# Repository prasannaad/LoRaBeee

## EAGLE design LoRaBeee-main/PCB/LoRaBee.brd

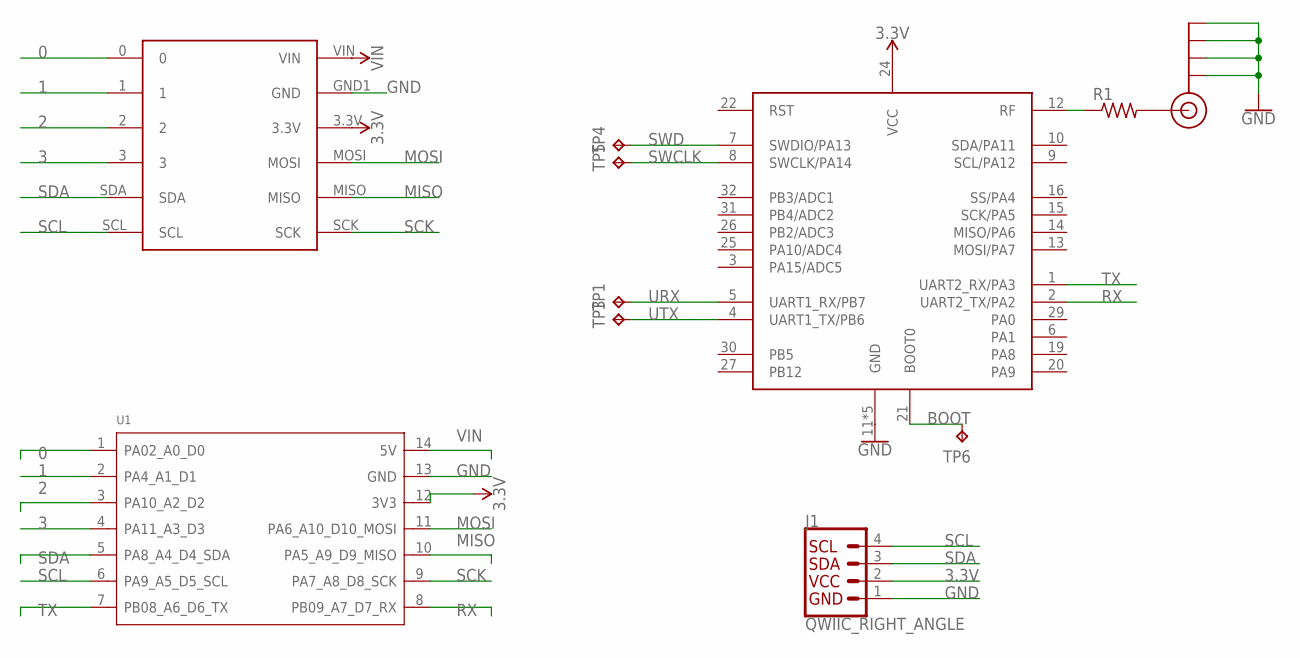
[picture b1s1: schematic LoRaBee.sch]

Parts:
J1: QWIIC_RIGHT_ANGLE; JST04_1MM_RA
J$1: SMA_EDGE; SMA-EDGE
R1: R-US_R0805; R0805
TP1, TP3, TP4, TP5, TP6: TPTP12R; TP12R
U1: MOUDLE-SEEEDUINO-XIAO; MOUDLE14P-2.54-21X17.8MM
U$1: BEEELINK
U$2: RAK3172HF; RAK3172

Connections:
0: U1.1 (PA02_A0_D0), U$1.0
1: U1.2 (PA4_A1_D1), U$1.1
2: U1.3 (PA10_A2_D2), U$1.2
3: U1.4 (PA11_A3_D3), U$1.3
3.3V: J1.2, U1.12 (3V3), U$1.3.3V, U$2.24 (VCC)
BOOT: TP6.TP, U$2.21 (BOOT0)
GND: J1.1, J$1.GND@0 (GND), J$1.GND@1 (GND), J$1.GND@2 (GND), J$1.GND@3 (GND), U1.13 (GND), U$1.GND1 (GND), U$2.11 (GND), U$2.17 (GND), U$2.18 (GND), U$2.23 (GND), U$2.28 (GND)
MISO: U1.10 (PA5_A9_D9_MISO), U$1.MISO
MOSI: U1.11 (PA6_A10_D10_MOSI), U$1.MOSI
unnamed: R1.1, U$2.12 (RF)
unnamed: J$1.SIG (SIGNAL), R1.2
RX: U1.8 (PB09_A7_D7_RX), U$2.2 (UART2_TX/PA2)
SCK: U1.9 (PA7_A8_D8_SCK), U$1.SCK
SCL: J1.4, U1.6 (PA9_A5_D5_SCL), U$1.SCL
SDA: J1.3, U1.5 (PA8_A4_D4_SDA), U$1.SDA
SWCLK: TP5.TP, U$2.8 (SWCLK/PA14)
SWD: TP4.TP, U$2.7 (SWDIO/PA13)
TX: U1.7 (PB08_A6_D6_TX), U$2.1 (UART2_RX/PA3)
URX: TP1.TP, U$2.5 (UART1_RX/PB7)
UTX: TP3.TP, U$2.4 (UART1_TX/PB6)
VIN: U1.14 (5V), U$1.VIN

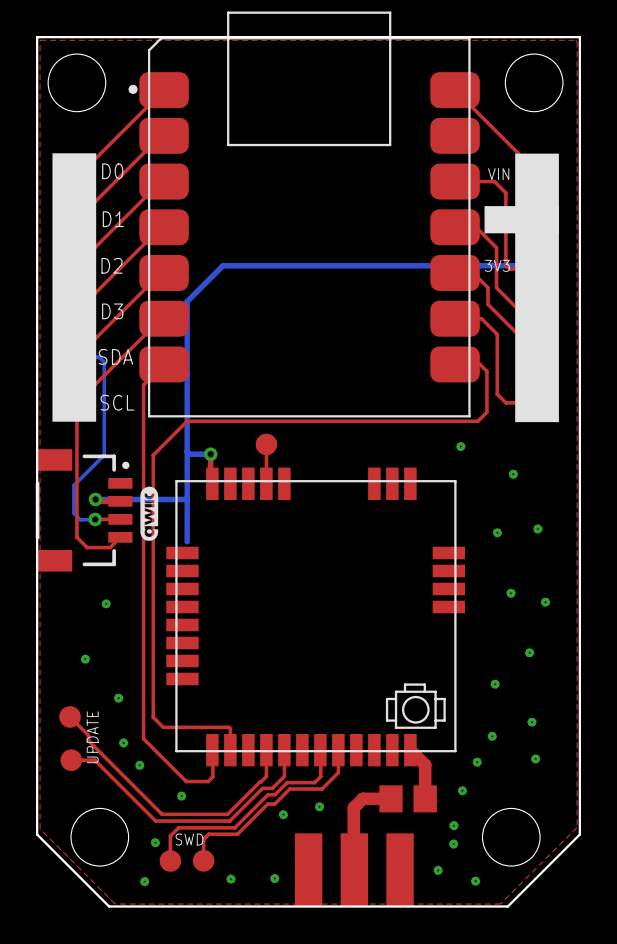
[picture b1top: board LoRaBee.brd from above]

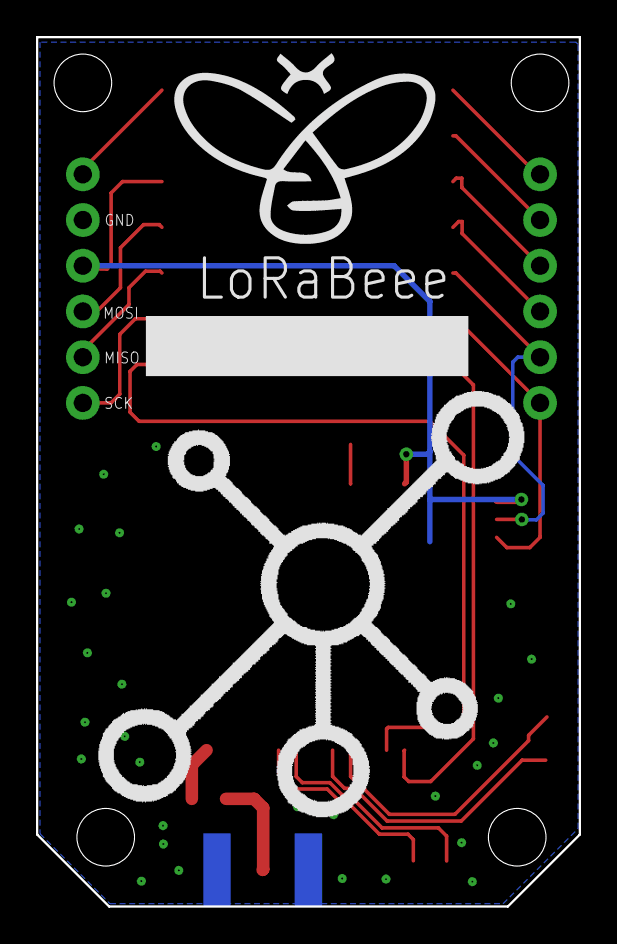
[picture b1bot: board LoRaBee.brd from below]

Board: 2 copper layers, 30.2 x 48.3 mm, 14 parts (2 on the bottom side), 21 nets.

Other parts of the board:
U$3: LOGO
U$4: BEEE_LOGO_M
U$5: QWIIC_3MM

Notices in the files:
parts and their libraries:
SparkFun-Retired: Licensing: Creative Commons ShareAlike 4.0 International - https://creativecommons.org/licenses/by-sa/4.0
